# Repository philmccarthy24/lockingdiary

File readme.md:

# Locking Diary
## DIY secure journal with numpad lock

*Phil McCarthy, May 2023*

### What is this project?

My daughter saw a diary in the toy shop with a number pad and electronic lock. I told her we weren't buying it - I could make one like that myself! She called my bluff... and didn’t forget about it. :grimacing:

So yes, making this will cost you much, much more in electronics components, 3D printing and PCB fabrication than it would cost to buy your child a cheap toy secret diary. But at least you made it yourself and had fun. :wink:

### Demo

See this video to see how the unit operates (TODO)
Instructable here: TODO

### What's included in this repository?

Original OpenSCAD designs and related assets for all parts, STL files for unmodified reprints (also Prusa project files which will save you time when slicing if you have a Prusa), KiCAD project files and gerbers for modifying/fabricating the PCB, and documentation.

Included in the documentation is [the full parts list](docs/BOM.md), [assembly instructions](docs/assembly.md), and [the printing settings that worked for me](docs/printing.md) when printing the parts out.

The rest of this readme contains information about the design choices for the project.

### Electrical Design

This is the first prototype for the electronics:

An SG90 servo moving an arm 90 degrees back/forth into a recess was chosen for the lock mechanism, due to:

- low cost
- fairly electrically efficient; 750mA **stall current** at 5v (much less unencombered) vs solenoid 1A+ for *normal operation*, with excess heat generated
- easy to control, just PWM signal
- self contained vs lead screw linear actuator; don’t need driving with mosfets / driver ICs
- No additional components required

A matrix style hobbyist number pad was chosen rather than wiring 12 momentary switches up manually; bang for buck the result is tidier and more tactile.

Arduino Nano Every MCU was chosen due to:

- High pin count - need 7 pins for number pad matrix circuit alone
- ability to drive PWM at 5v without needing extra logic level conversion
- doesn’t need to be particularly fast/high powered/lots of memory.

For power, need headroom for 1A (~60mA for RGB LED, 20mA for Arduino and 750mA max for servo). To keep cost down, but battery footprint compact, AAA batteries can be positioned down the spine of the diary. An Adafruit Miniboost 5V module converts 2-6V into 5V regulated, and supplies ~1A. rechargeable AAAs are 950+mAh, 1.2vx3 = 3.6v (1100mA from Miniboost at this V) which is more than sufficient. Micro slide switch pulls the enable pin on mini boost active low / ground to stop power supply efficiently.

The Arduino's VIN pin takes 7-21v due to builtin voltage regulator. We already have a regulated 5v supply, so using the 5v output pin as an input to avoid extra DC up-conversion components as space is limited; need to make PCB as small and low profile as possible. (5v pin as input not recommended, and voltage fluctuations can lead to MCU processor damage according to forum posts, but can't source specific technical doumentation that says this can't be done with a single regulated supply where the USB won't be used in conjunction. On testing it seems to work fine).

### Firmware design

For persistent state, can use Nano Every’s EEPROM to store new pin when lock is open (by pressing # key 3 times). RGB led provides feedback about mode the lock is in - blue for “enter new pin”, green for unlocked, red for locked.

**TODO TODO TODO**

### Mechanical Design

rectangular pcb and mount / glue keypad on top. runs can be under keypad, and servo connector can be in vertical middle
pcbs mounted to book cover using M5 chicago screws, with 3D printed fascia on top

### Legal stuff
This project is not a commercial product. The designs are made available free and open source. The PCB design, CAD models and microcontroller firmware are shared under the [GPLv3 license](https://www.gnu.org/licenses/gpl-3.0.en.html). Please don't assume anything works, for any particular purpose. Built completely at your own risk.

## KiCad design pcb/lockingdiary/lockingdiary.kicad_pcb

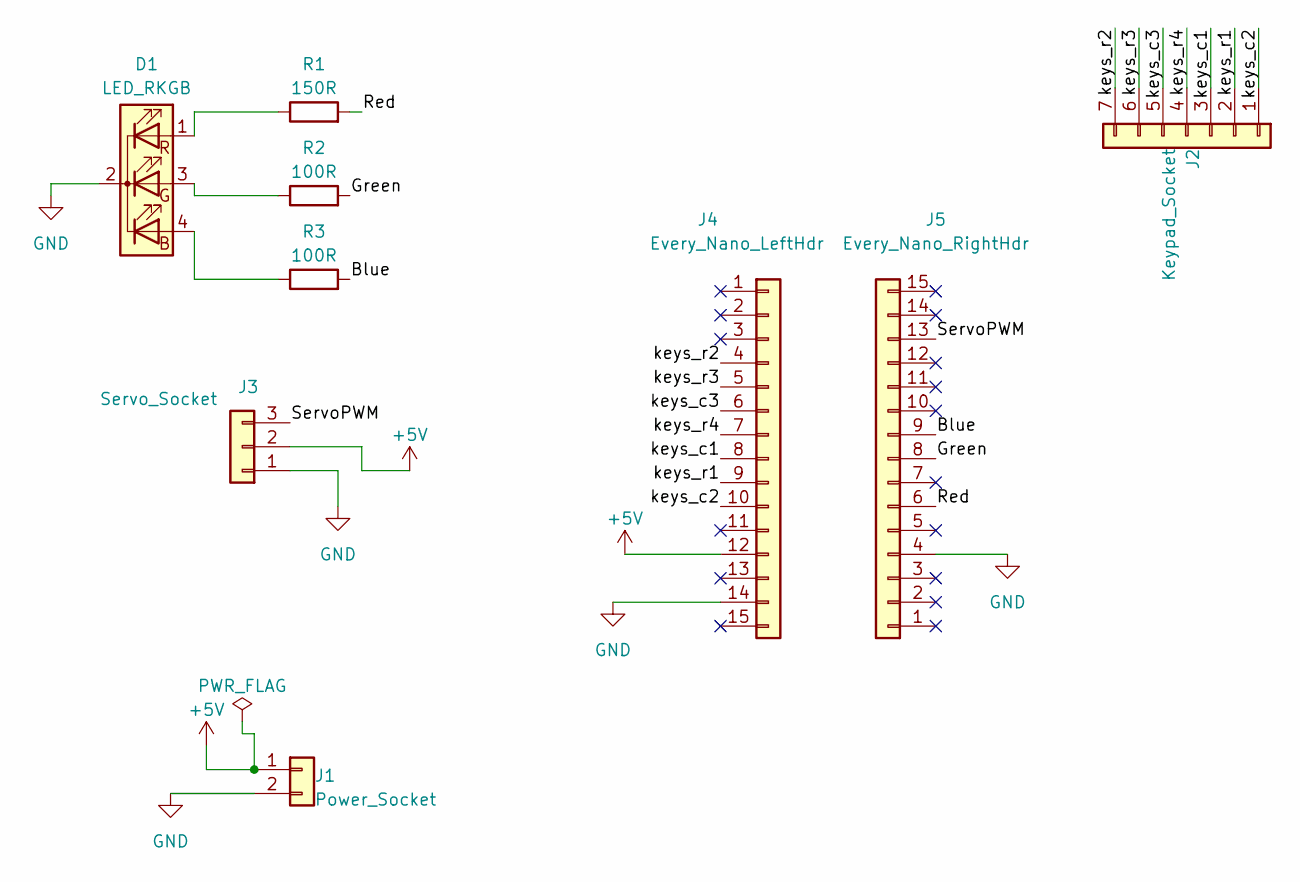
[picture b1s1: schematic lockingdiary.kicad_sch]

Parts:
D1: LED_RKGB; LED_D5.0mm-4_RGB
J1: Power_Socket; JST_PH_S2B-PH-K_1x02_P2.00mm_Horizontal
J2: Keypad_Socket; PinSocket_1x07_P2.54mm_Vertical
J3: Servo_Socket; JST_PH_S3B-PH-K_1x03_P2.00mm_Horizontal
J4: Every_Nano_LeftHdr; PinSocket_1x15_P2.54mm_Vertical
J5: Every_Nano_RightHdr; PinSocket_1x15_P2.54mm_Vertical
R1: 150R; R_Axial_DIN0207_L6.3mm_D2.5mm_P10.16mm_Horizontal
R2, R3: 100R; R_Axial_DIN0207_L6.3mm_D2.5mm_P10.16mm_Horizontal

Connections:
+5V: J1.1, J3.2, J4.12
/Blue: J5.9, R3.2
/Green: J5.8, R2.2
/Red: J5.6, R1.2
/ServoPWM: J3.3, J5.13
/keys_c1: J2.3, J4.8
/keys_c2: J2.1, J4.10
/keys_c3: J2.5, J4.6
/keys_r1: J2.2, J4.9
/keys_r2: J2.7, J4.4
/keys_r3: J2.6, J4.5
/keys_r4: J2.4, J4.7
GND: D1.2 (K), J1.2, J3.1, J4.14, J5.4
unnamed: D1.4 (BA), R3.1
unnamed: D1.3 (GA), R2.1
unnamed: D1.1 (RA), R1.1

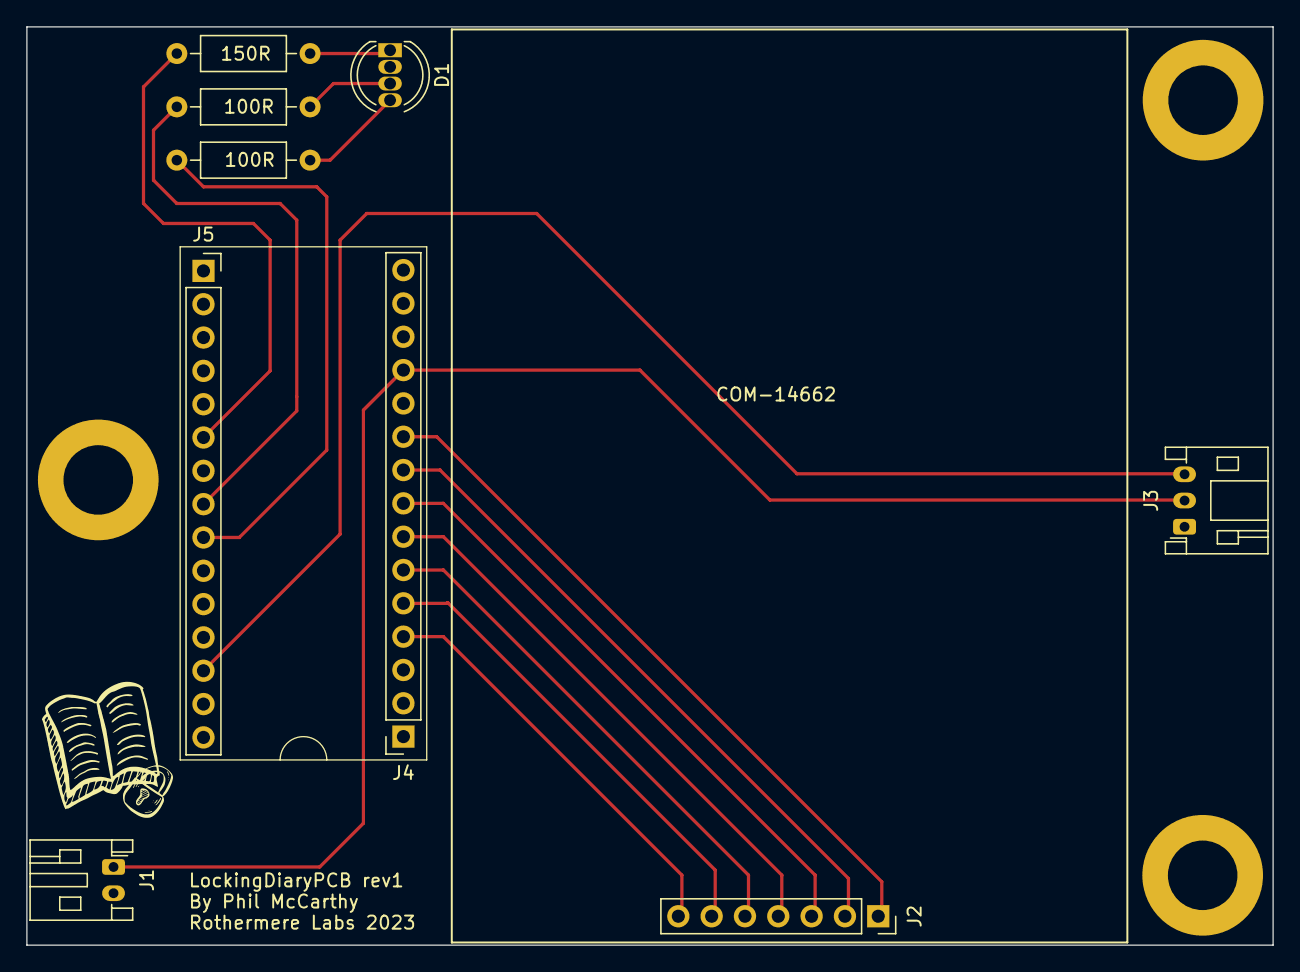
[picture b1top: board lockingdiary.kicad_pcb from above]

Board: 2 copper layers, 95.0 x 70.0 mm, 9 parts (0 on the bottom side), 16 nets.

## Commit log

2023-04-30 Finished firmware for lock controller
2023-05-07 Finished spine battery pack design. Started on PCB design
2023-05-08 Finished rev1 PCB design. Started on readme and docs
2023-05-22 Designed fascia plate - prototype needs tweaks
2025-05-03 Some design improvements for Emma's diary
